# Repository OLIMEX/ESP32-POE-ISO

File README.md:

# ESP32-POE-ISO

ESP32-PoE-ISO is an IoT WIFI/BLE/Ethernet development board with Power-Over-Ethernet feature. The Si3402-B chip is IEEE 802.3-compliant, including pre-standard (legacy) PoE support. Perfect solution for Internet-of-Things that can be expanded with sensors and actuators taking power from Ethernet cable.

ESP32-POE-ISO has 3000VDC galvanic insulation from the Ethernet.

Product page: https://www.olimex.com/Products/IoT/ESP32/ESP32-POE-ISO/open-source-hardware

LICENSEE:

ESP32-POE-ISO is Open Source Hardware as per OSHWA.org definition. It is distributed with CERN OSH Licensee v1.2 which is available in the root directory of this repository.

The software examples for ESP32-POE-ISO are distributed with GPL v3 Licensee.

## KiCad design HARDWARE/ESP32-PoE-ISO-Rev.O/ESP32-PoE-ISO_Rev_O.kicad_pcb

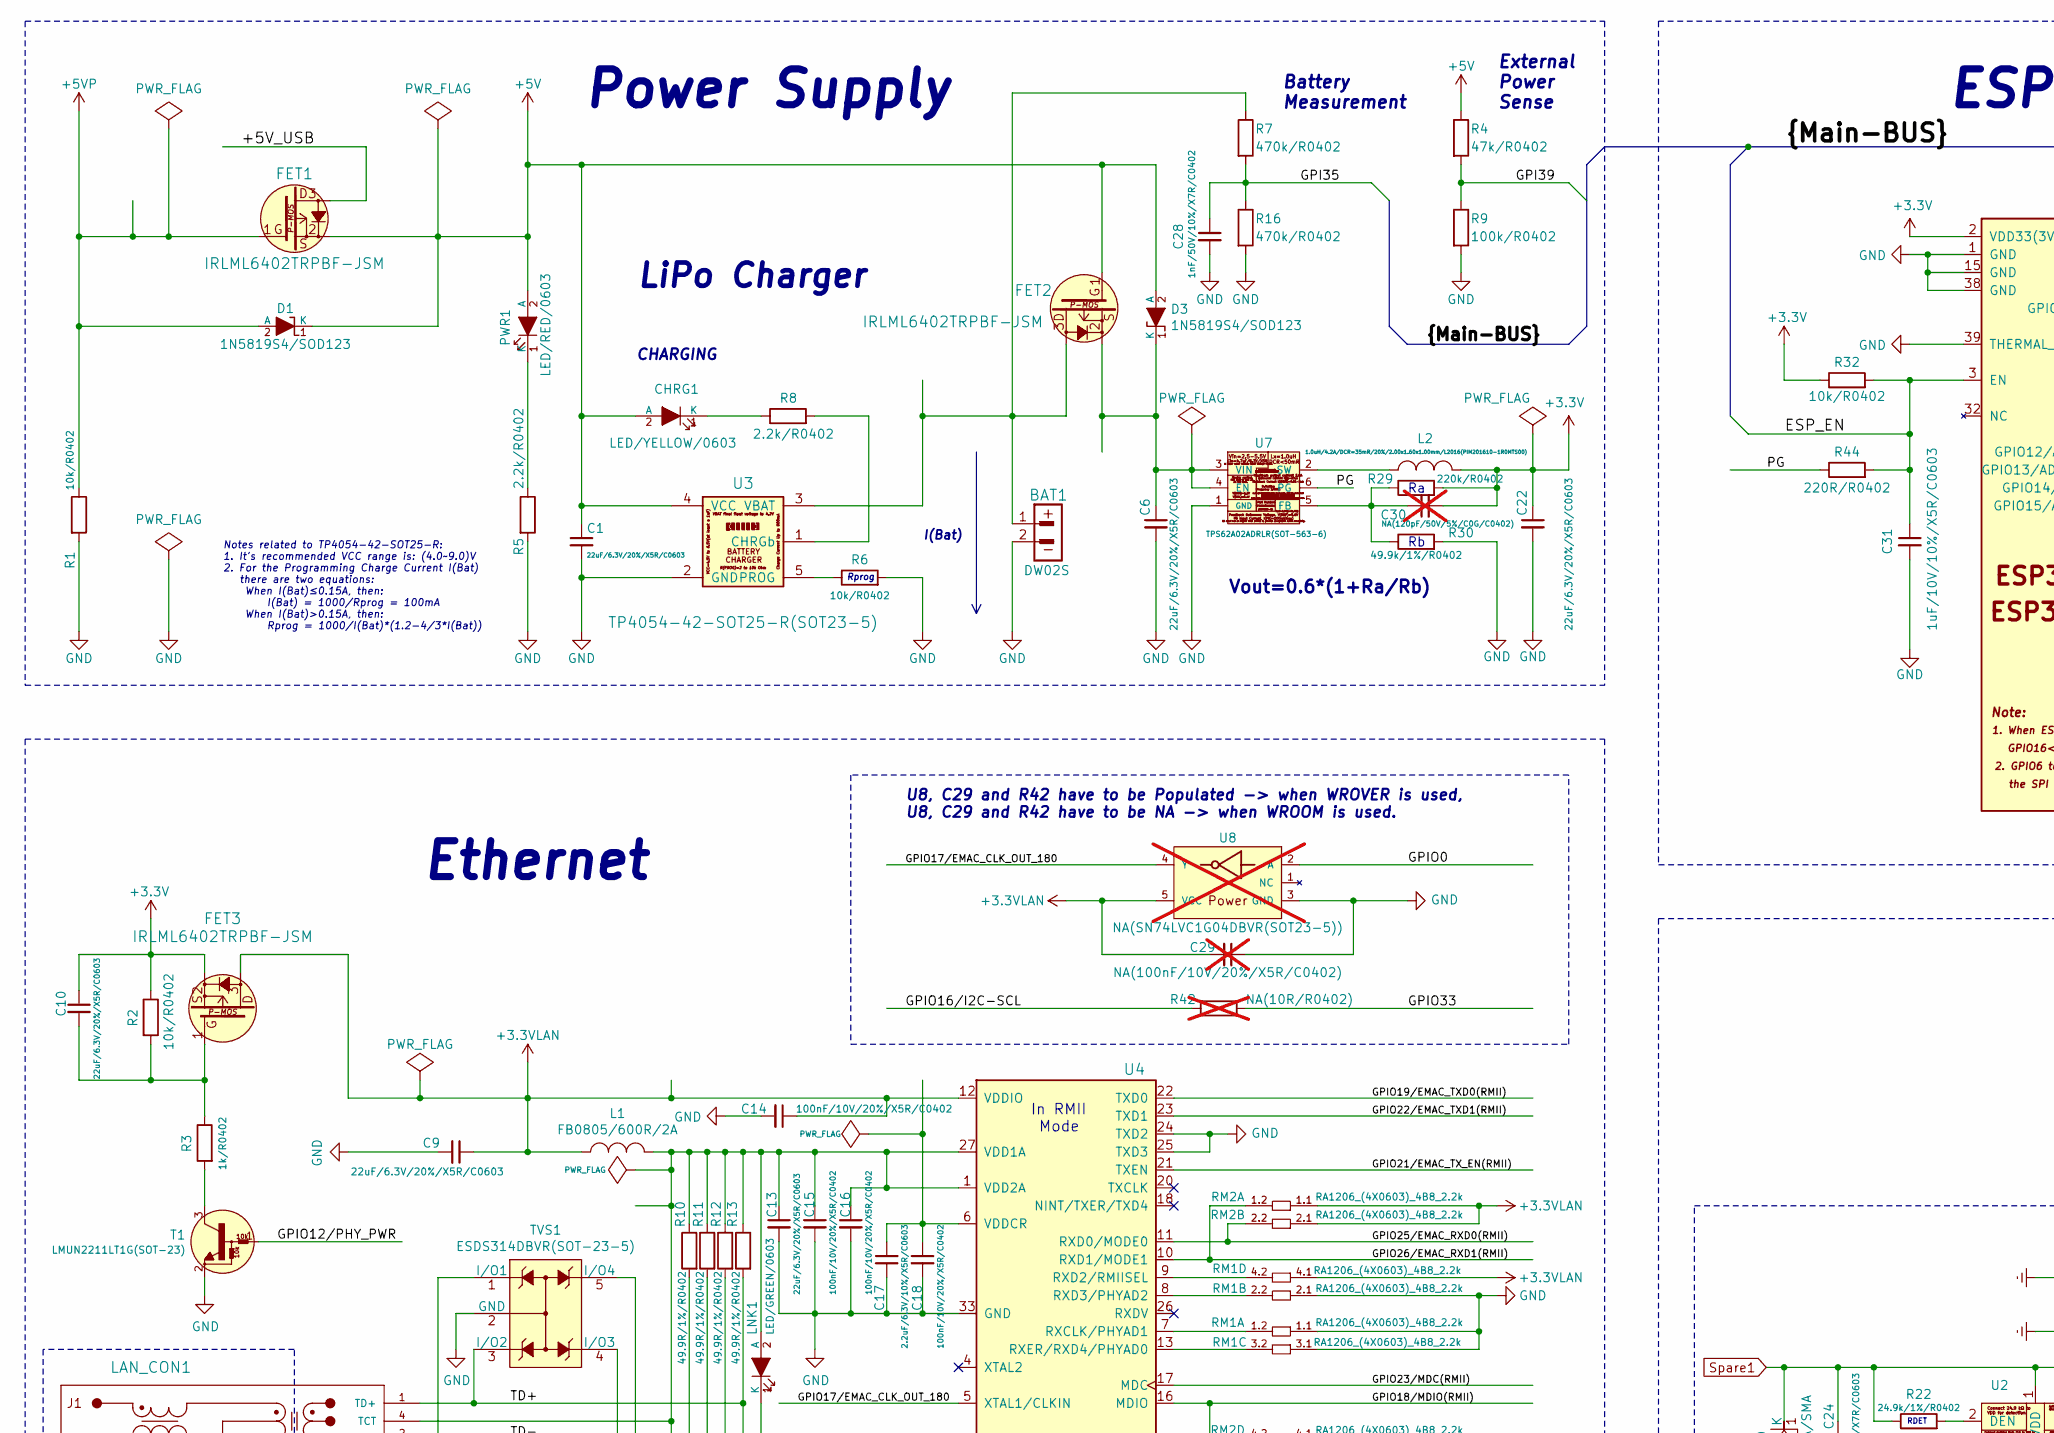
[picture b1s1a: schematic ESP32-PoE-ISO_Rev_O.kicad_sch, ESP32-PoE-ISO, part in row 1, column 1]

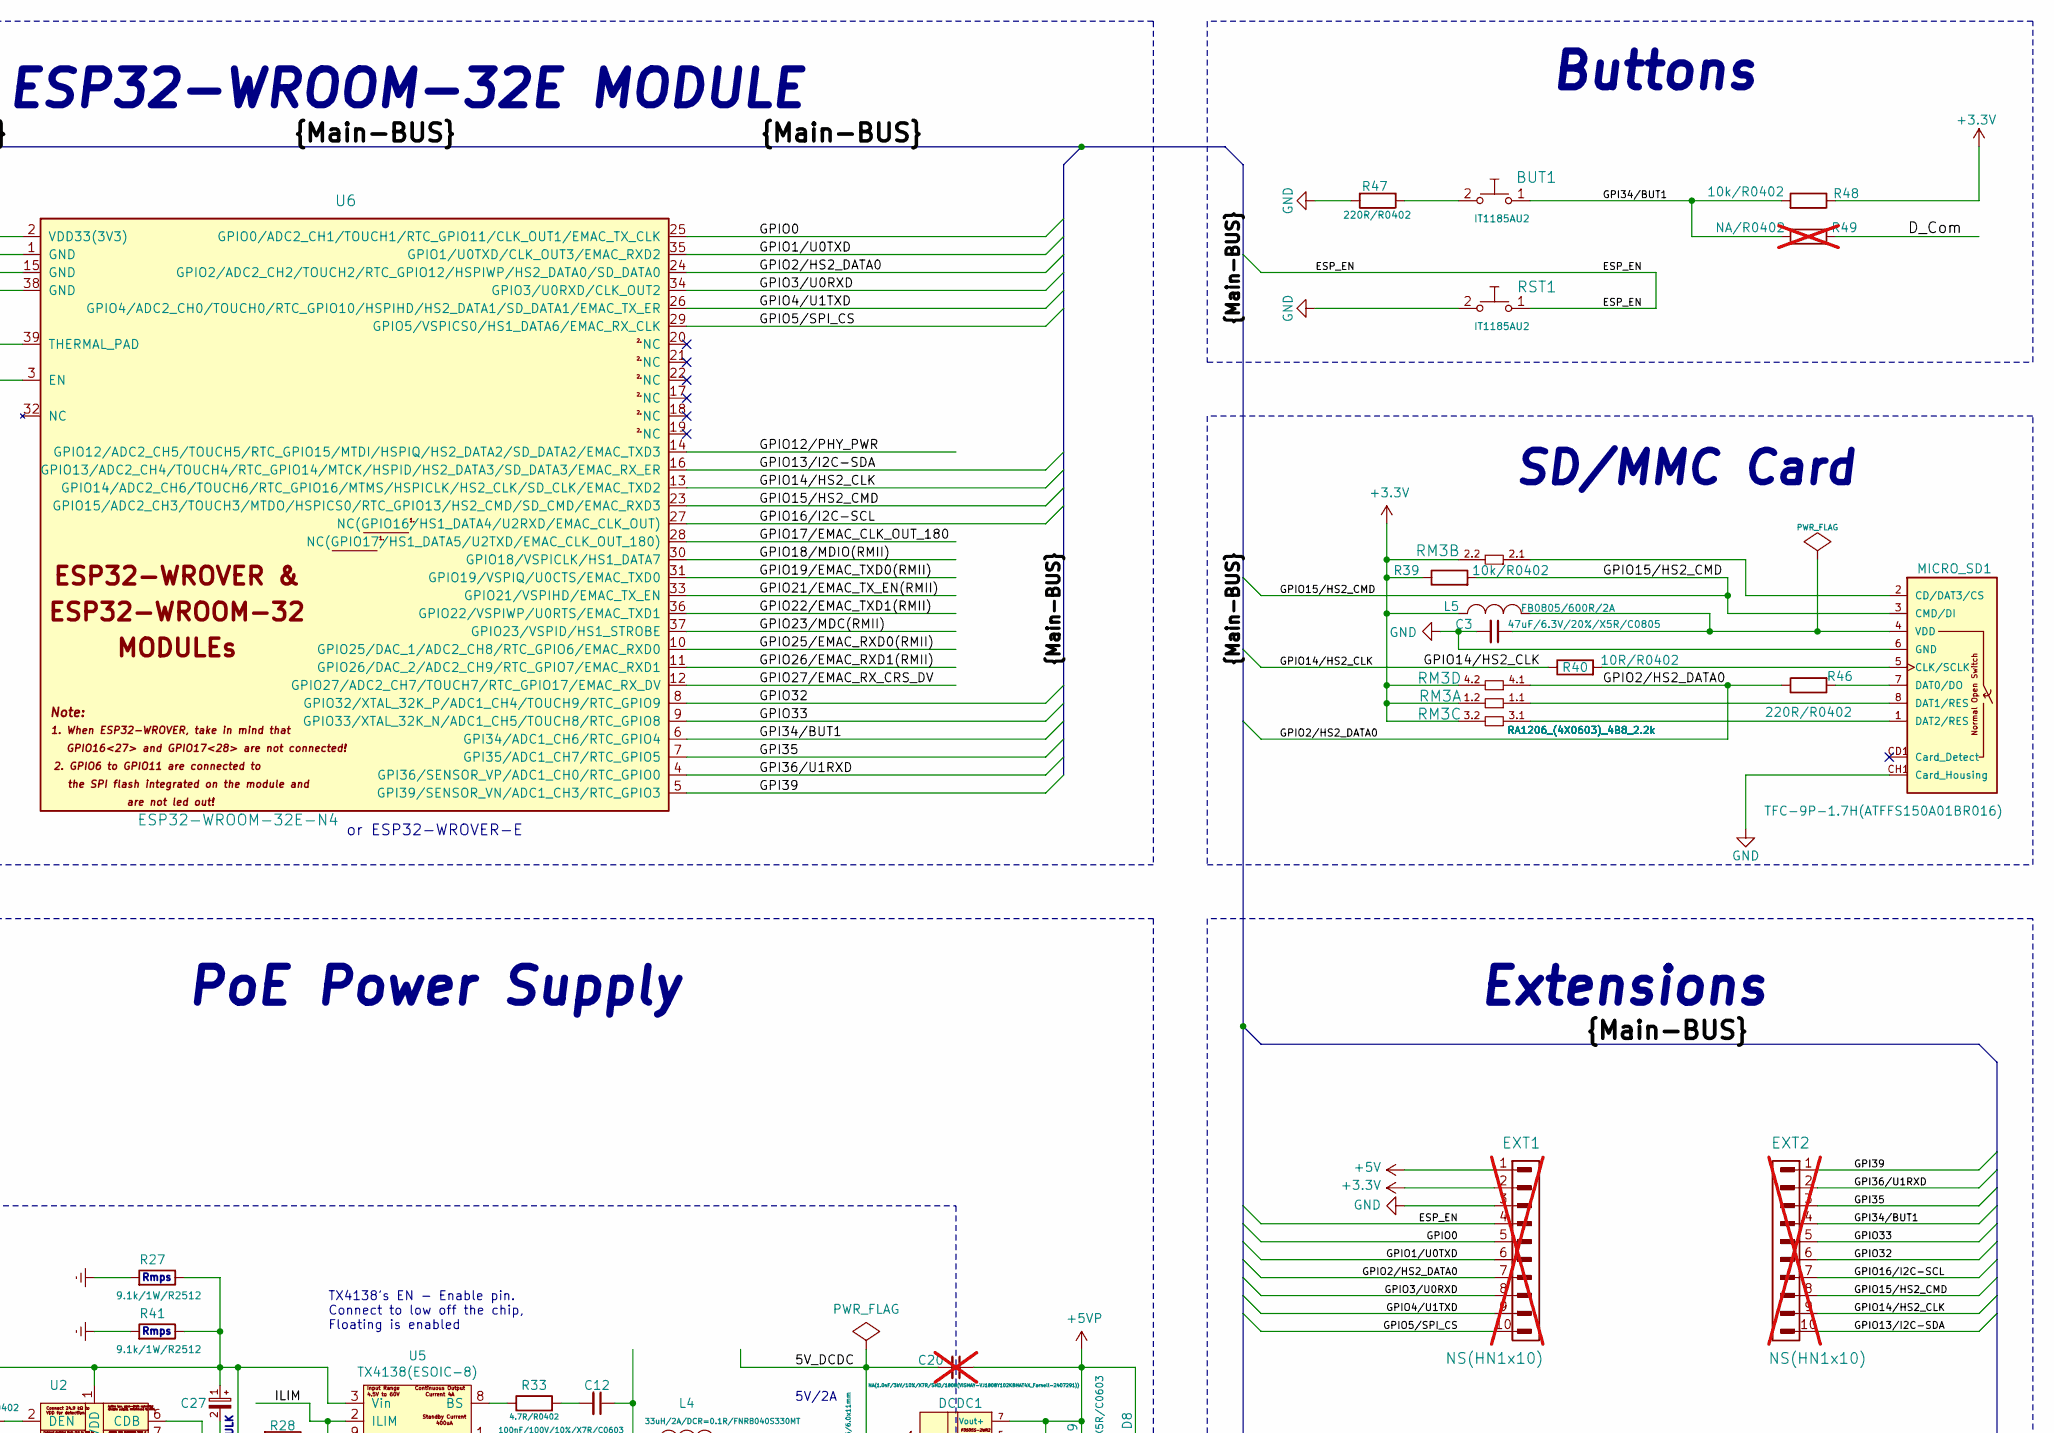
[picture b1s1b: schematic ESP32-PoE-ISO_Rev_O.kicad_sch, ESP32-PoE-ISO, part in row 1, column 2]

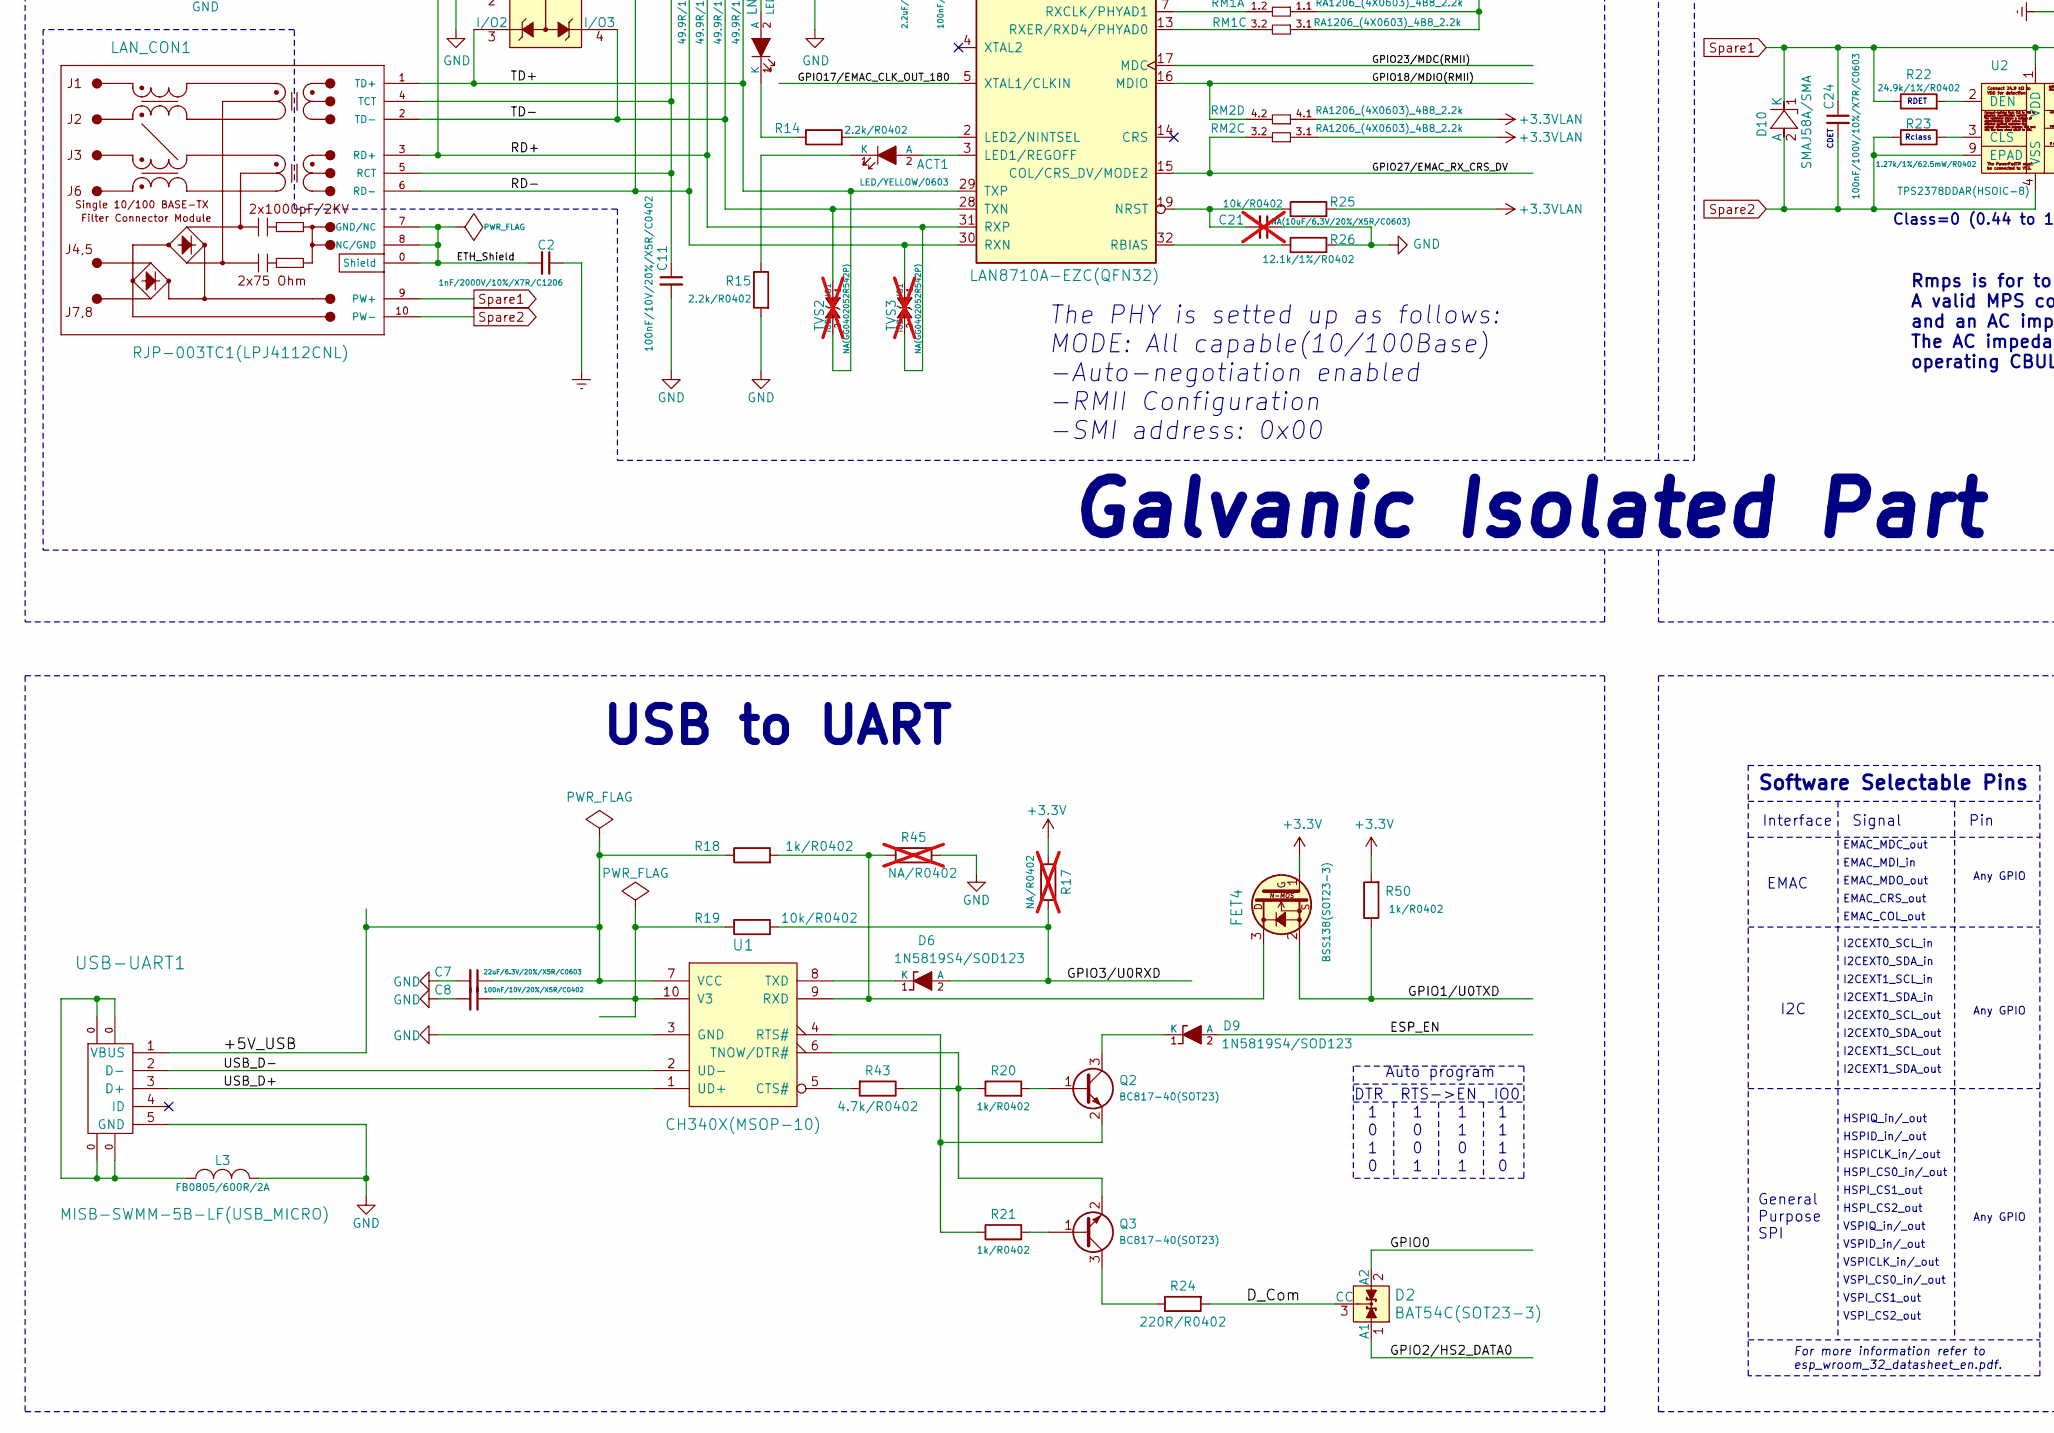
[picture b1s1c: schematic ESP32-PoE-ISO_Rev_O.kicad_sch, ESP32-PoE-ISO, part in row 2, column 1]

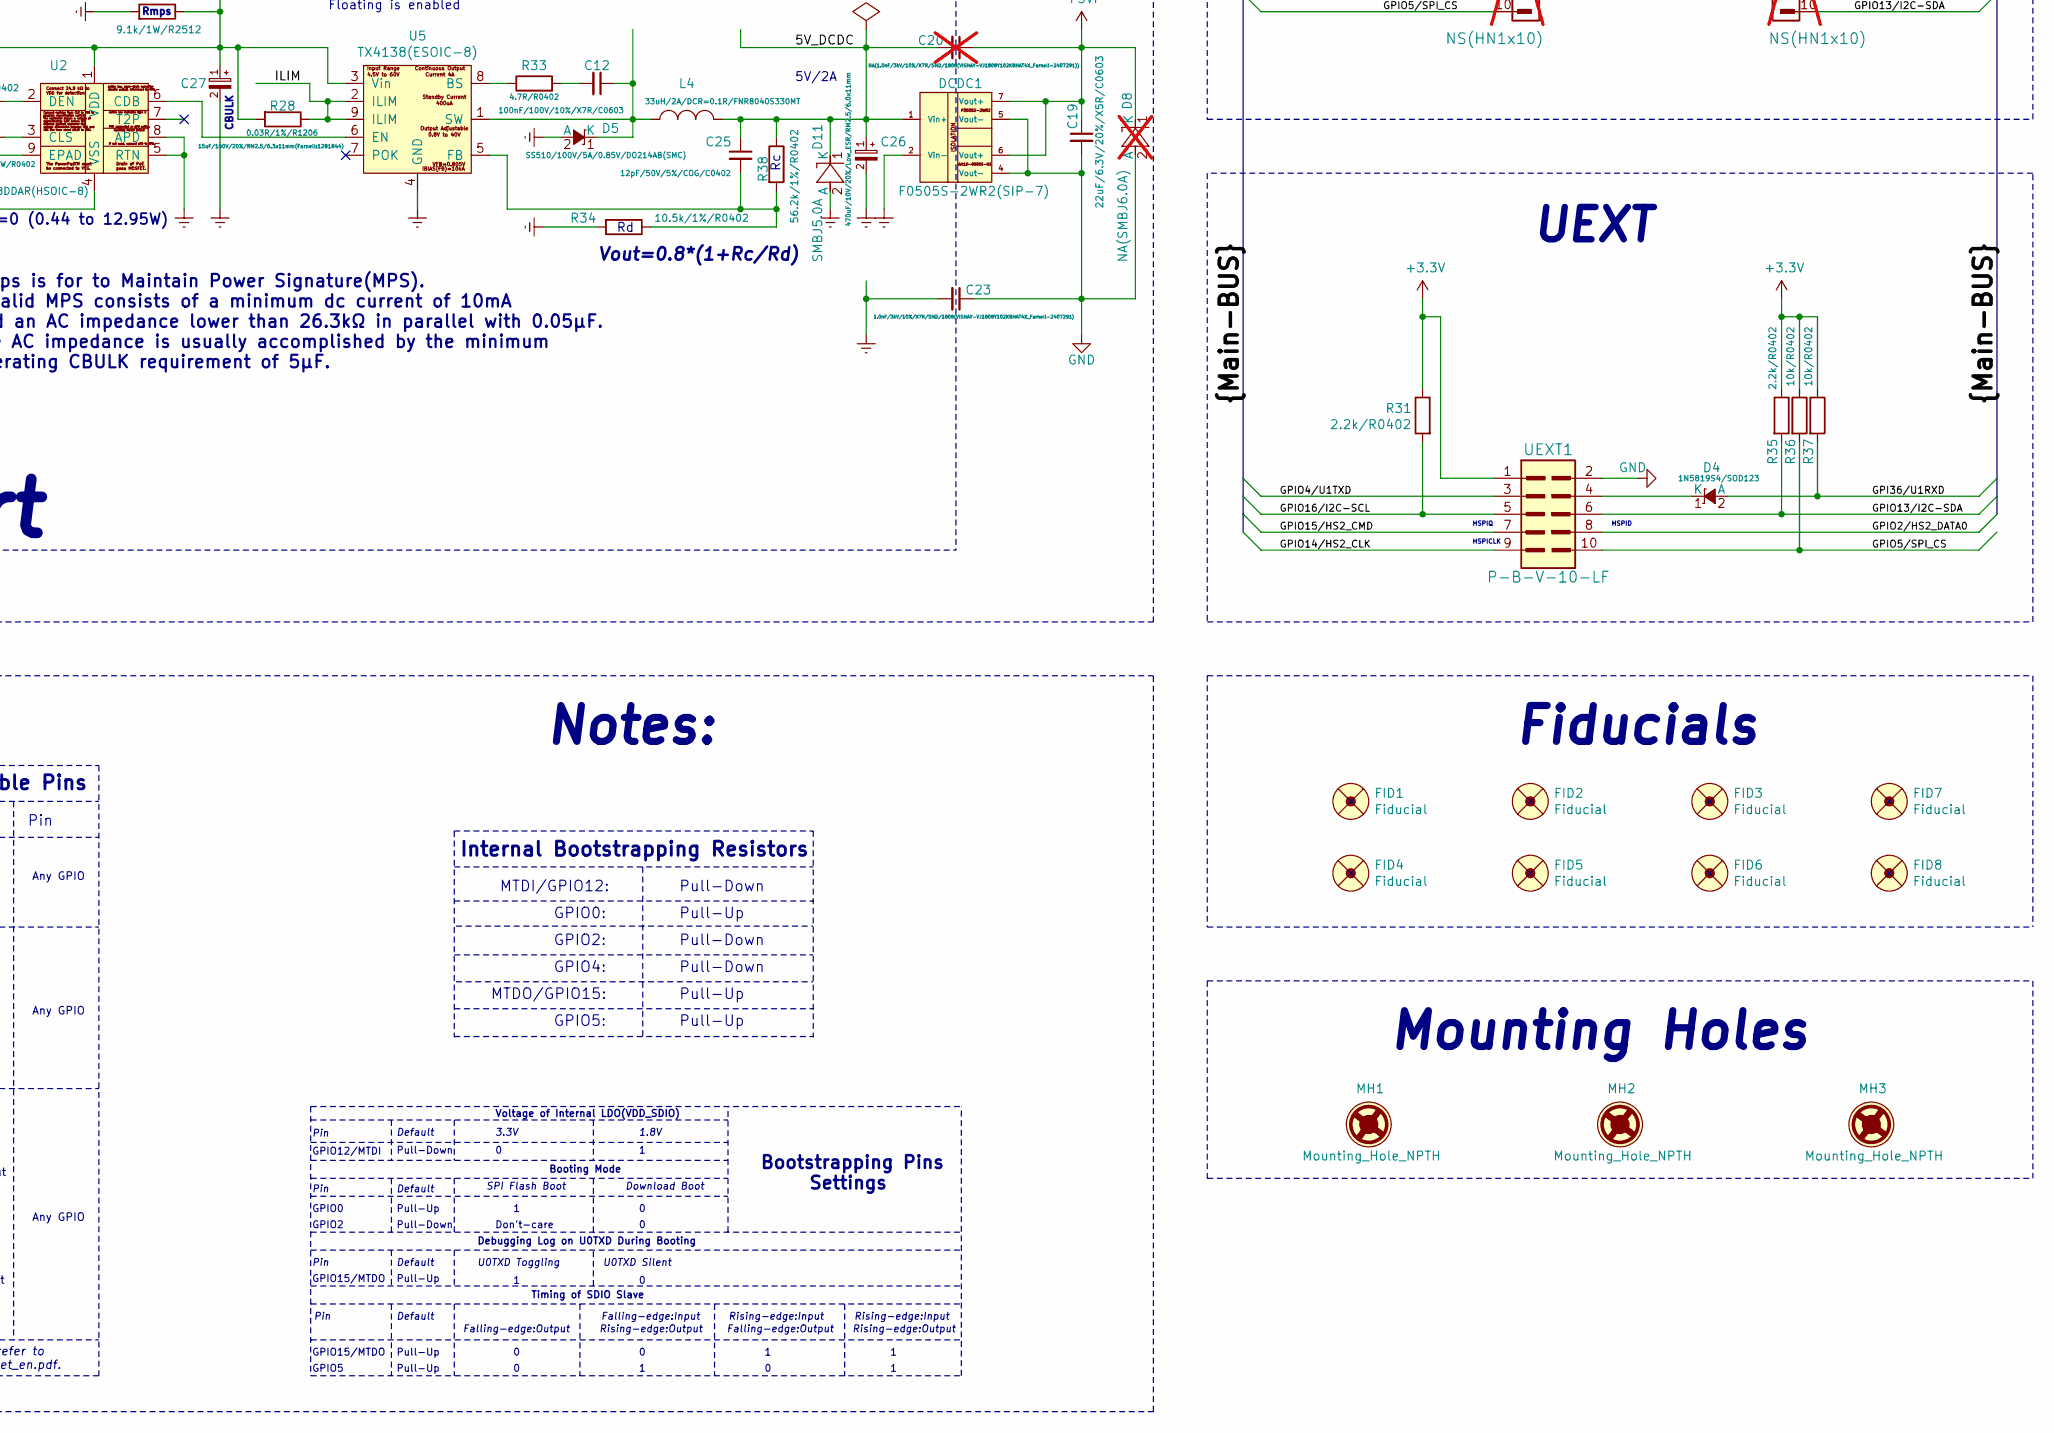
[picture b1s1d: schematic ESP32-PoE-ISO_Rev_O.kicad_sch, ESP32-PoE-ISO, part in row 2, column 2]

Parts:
ACT1: LED/YELLOW/0603; LED_0603_KA
BAT1: DW02S; LIPO_BAT_VERTICAL_DW02S
BUT1: IT1185AU2; IT1185AU2_V2
C1, C6, C7, C9, C10, C13, C19, C22: 22uF/6.3V/20%/X5R/C0603; C_0603_5MIL_DWS
C2: 1nF/2000V/10%/X7R/C1206; C_1206_5MIL_DWS_ISO
C3: 47uF/6.3V/20%/X5R/C0805; C_0805_5MIL_DWS
C8, C11, C14, C15, C16, C18: 100nF/10V/20%/X5R/C0402; C_0402_5MIL_DWS
C12, C24: 100nF/100V/10%/X7R/C0603; C_0603_5MIL_DWS
C17: 2.2uF/6.3V/10%/X5R/C0603; C_0603_5MIL_DWS
C20: NA(1.0nF/3kV/10%/X7R/SMD/1808(VISHAY-VJ1808Y102KB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; C_1808(4520)_5MIL_DWS_ISO; not fitted
C21: NA(10uF/6.3V/20%/X5R/C0603); C_0603_5MIL_DWS; not fitted
C23: 1.0nF/3kV/10%/X7R/SMD/1808(VISHAY-VJ1808Y102KBHAT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; C_1808(4520)_5MIL_DWS_ISO
C25: 12pF/50V/5%/COG/C0402; C_0402_5MIL_DWS
C26: 470uF/10V/20%/Low_ESR/RM2.5/6.0x11mm; CPOL-RM2.5mm_6.3x11mm_PTH
C27: 15uF/100V/20%/RM2.5/6.3x11mm(Farnell:1281844); CPOL-RM2.5mm_6.3x11mm_PTH
C28: 1nF/50V/10%/X7R/C0402; C_0402_5MIL_DWS
C29: NA(100nF/10V/20%/X5R/C0402); C_0402_5MIL_DWS; not fitted
C30: NA(120pF/50V/5%/C0G/C0402); C_0402_5MIL_DWS; not fitted
C31: 1uF/10V/10%/X5R/C0603; C_0603_5MIL_DWS
CHRG1: LED/YELLOW/0603; LED_0603_KA
D1, D3, D4, D6, D9: 1N5819S4/SOD123; SOD-123_1C-2A_KA
D2: BAT54C(SOT23-3); SOT23-3
D5: SS510/100V/5A/0.85V/DO214AB(SMC); DO214AB(SMC)_1(K)-2(A)
D8: NA(SMBJ6.0A); DO214AA_1(K)-2(A); not fitted
D10: SMAJ58A/SMA; SMA-KA
D11: SMBJ5.0A; DO214AA_1(K)-2(A)
DCDC1: F0505S-2WR2(SIP-7); SIP-7_Universal
EXT1, EXT2: NS(HN1x10); HN1x10; not fitted
FET1, FET2, FET3: IRLML6402TRPBF-JSM; SOT23
FET4: BSS138(SOT23-3); SOT23
FID1, FID4, FID7, FID8: Fiducial; Fiducial1x3_Paste
FID2, FID3, FID5, FID6: Fiducial; Fiducial1x3
L1, L3, L5: FB0805/600R/2A; L_0805_5MIL_DWS
L2: 1.0uH/4.2A/DCR=35mR/20%/2.00x1.60x1.00mm/L2016(PI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; L_2016_MM
L4: 33uH/2A/DCR=0.1R/FNR8040S330MT; FNR8040S
LAN_CON1: RJP-003TC1(LPJ4112CNL)
LNK1: LED/GREEN/0603; LED_0603_KA
MH1, MH2, MH3: Mounting_Hole_NPTH; NPTH_2.2mm
MICRO_SD1: TFC-9P-1.7H(ATFFS150A01BR016); uSD(TFC-9P-1.xH(ATFFS150A01BR016))
PWR1: LED/RED/0603; LED_0603_KA
Q2, Q3: BC817-40(SOT23); SOT23
R1, R2, R6, R19, R25, R32, R36, R37, R39, R48: 10k/R0402; R_0402_5MIL_DWS
R3, R18, R20, R21, R50: 1k/R0402; R_0402_5MIL_DWS
R4: 47k/R0402; R_0402_5MIL_DWS
R5, R8, R14, R15, R31, R35: 2.2k/R0402; R_0402_5MIL_DWS
R7, R16: 470k/R0402; R_0402_5MIL_DWS
R9: 100k/R0402; R_0402_5MIL_DWS
R10, R11, R12, R13: 49.9R/1%/R0402; R_0402_5MIL_DWS
R17, R45, R49: NA/R0402; R_0402_5MIL_DWS; not fitted
R22: 24.9k/1%/R0402; R_0402_5MIL_DWS
R23: 1.27k/1%/62.5mW/R0402; R_0402_5MIL_DWS
R24, R44, R46, R47: 220R/R0402; R_0402_5MIL_DWS
R26: 12.1k/1%/R0402; R_0402_5MIL_DWS
R27, R41: 9.1k/1W/R2512; R_2512_MM_DWS
R28: 0.03R/1%/R1206; R_1206_5MIL_DWS
R29: 220k/R0402; R_0402_5MIL_DWS
R30: 49.9k/1%/R0402; R_0402_5MIL_DWS
R33: 4.7R/R0402; R_0402_5MIL_DWS
R34: 10.5k/1%/R0402; R_0402_5MIL_DWS
R38: 56.2k/1%/R0402; R_0402_5MIL_DWS
R40: 10R/R0402; R_0402_5MIL_DWS
R42: NA(10R/R0402); R_0402_5MIL_DWS; not fitted
R43: 4.7k/R0402; R_0402_5MIL_DWS
RM1, RM2, RM3: RA1206_(4X0603)_4B8_2.2k; R_MATRIX_4
RST1: IT1185AU2; IT1185AU2_V2
T1: LMUN2211LT1G(SOT-23); SOT23
TVS1: ESDS314DBVR(SOT-23-5); SOT-23-5
TVS2, TVS3: NA(GG0402052R542P); D_0402_5MIL_DWS; not fitted
U1: CH340X(MSOP-10); MSOP-10_Pitch-0.5mm_3.00x3.00x1.00mm
U2: TPS2378DDAR(HSOIC-8); ESOIC-8
U3: TP4054-42-SOT25-R(SOT23-5); SOT-23-5
U4: LAN8710A-EZC(QFN32); QFN32_EP(33)_5.00x5.00x0.90mm_Pitch_0.50mm
U5: TX4138(ESOIC-8); ESOIC-8
U6: ESP32-WROOM-32E-N4; ESP32-WROVER_MODULE
U7: TPS62A02ADRLR(SOT-563-6); SOT-563-6
U8: NA(SN74LVC1G04DBVR(SOT23-5)); SOT-23-5; not fitted
UEXT1: P-B-V-10-LF; GBH-254-SMT-10
USB-UART1: MISB-SWMM-5B-LF(USB_MICRO); USB-MICRO_MISB-SWMM-5B_LF

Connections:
+3.3V: C10.1, C22.1, C30.2, EXT1.2, FET3.2, FET4.1 (G), L2.2, L5.1, R2.1, R17.1, R29.2, R31.1, R32.1, R35.1, R36.1, R37.1, R39.1, R48.1, R50.2, RM3.1.2, RM3.2.2, RM3.3.2, RM3.4.2, U6.2 (VDD33(3V3)), UEXT1.1
+3.3VLAN: C9.1, C14.1, C29.2, FET3.3, L1.1, R25.2, RM1.4.1, RM2.1.1, RM2.2.1, RM2.3.1, RM2.4.1, U4.12 (VDDIO), U8.5 (VCC)
+5V: C1.1, CHRG1.2 (A), D1.1 (K), D3.2 (A), EXT1.1, FET1.2, FET2.1, PWR1.2 (A), R4.1, U3.4 (VCC)
+5VP: C19.1, C20.1, D1.2 (A), D8.1 (K), DCDC1.6 (Vout+), DCDC1.7 (Vout+), FET1.1, R1.1
/5V_DCDC: C20.2, C25.1, C26.1 (+), D11.1 (K), DCDC1.1 (Vin+), L4.2, R38.1
/+5V_USB: C7.1, FET1.3, R18.1, U1.7 (VCC), USB-UART1.1 (VBUS)
/D_Com: D2.3 (CC), R24.2, R49.2
/ESP_EN: C31.1, D9.2 (A), EXT1.4, R32.2, R44.2, RST1.1, U6.3 (EN)
/ETH_Shield: C2.2, LAN_CON1.0 (Shield), LAN_CON1.7 (GND/NC), LAN_CON1.8 (NC/GND)
/GPI34/BUT1: BUT1.1, EXT2.4, R48.2, R49.1, U6.6 (GPI34/ADC1_CH6/RTC_GPIO4)
/GPI35: C28.1, EXT2.3, R7.2, R16.1, U6.7 (GPI35/ADC1_CH7/RTC_GPIO5)
/GPI36/U1RXD: D4.2 (A), EXT2.2, R37.2, U6.4 (GPI36/SENSOR_VP/ADC1_CH0/RTC_GPIO0)
/GPI39: EXT2.1, R4.2, R9.1, U6.5 (GPI39/SENSOR_VN/ADC1_CH3/RTC_GPIO3)
/GPIO0: D2.2 (A2), EXT1.5, U6.25 (GPIO0/ADC2_CH1/TOUCH1/RTC_GPIO11/CLK_OU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), U8.2 (A)
/GPIO1/U0TXD: EXT1.6, FET4.2 (S), R50.1, U6.35 (GPIO1/U0TXD/CLK_OUT3/EMAC_RXD2)
/GPIO2/HS2_DATA0: D2.1 (A1), EXT1.7, R46.1, RM3.4.1, U6.24 (GPIO2/ADC2_CH2/TOUCH2/RTC_GPIO12/HSPIWP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), UEXT1.8
/GPIO3/U0RXD: D6.2 (A), EXT1.8, R17.2, R19.2, U6.34 (GPIO3/U0RXD/CLK_OUT2)
/GPIO4/U1TXD: EXT1.9, U6.26 (GPIO4/ADC2_CH0/TOUCH0/RTC_GPIO10/HSPIHD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), UEXT1.3
/GPIO5/SPI_CS: EXT1.10, R36.2, U6.29 (GPIO5/VSPICS0/HS1_DATA6/EMAC_RX_CLK), UEXT1.10
/GPIO12/PHY_PWR: T1.1 (B), U6.14 (GPIO12/ADC2_CH5/TOUCH5/RTC_GPIO15/MTDI/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)
/GPIO13/I2C-SDA: EXT2.10, R35.2, U6.16 (GPIO13/ADC2_CH4/TOUCH4/RTC_GPIO14/MTCK/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), UEXT1.6
/GPIO14/HS2_CLK: EXT2.9, R40.1, U6.13 (GPIO14/ADC2_CH6/TOUCH6/RTC_GPIO16/MTMS/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), UEXT1.9
/GPIO15/HS2_CMD: EXT2.8, MICRO_SD1.3 (CMD/DI), R39.2, U6.23 (GPIO15/ADC2_CH3/TOUCH3/MTDO/HSPICS0/RTC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), UEXT1.7
/GPIO16/I2C-SCL: EXT2.7, R31.2, R42.2, U6.27 (NC(GPIO16/HS1_DATA4/U2RXD/EMAC_CLK_OUT)), UEXT1.5
/GPIO17/EMAC_CLK_OUT_180: U4.5 (XTAL1/CLKIN), U6.28 (NC(GPIO17/HS1_DATA5/U2TXD/EMAC_CLK_OUT_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), U8.4 (Y)
/GPIO18/MDIO(RMII): RM2.4.2, U4.16 (MDIO), U6.30 (GPIO18/VSPICLK/HS1_DATA7)
/GPIO19/EMAC_TXD0(RMII): U4.22 (TXD0), U6.31 (GPIO19/VSPIQ/U0CTS/EMAC_TXD0)
/GPIO21/EMAC_TX_EN(RMII): U4.21 (TXEN), U6.33 (GPIO21/VSPIHD/EMAC_TX_EN)
/GPIO22/EMAC_TXD1(RMII): U4.23 (TXD1), U6.36 (GPIO22/VSPIWP/U0RTS/EMAC_TXD1)
/GPIO23/MDC(RMII): U4.17 (MDC), U6.37 (GPIO23/VSPID/HS1_STROBE)
/GPIO25/EMAC_RXD0(RMII): RM2.2.2, U4.11 (RXD0/MODE0), U6.10 (GPIO25/DAC_1/ADC2_CH8/RTC_GPIO6/EMAC_RX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)
/GPIO26/EMAC_RXD1(RMII): RM2.1.2, U4.10 (RXD1/MODE1), U6.11 (GPIO26/DAC_2/ADC2_CH9/RTC_GPIO7/EMAC_RX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)
/GPIO27/EMAC_RX_CRS_DV: RM2.3.2, U4.15 (COL/CRS_DV/MODE2), U6.12 (GPIO27/ADC2_CH7/TOUCH7/RTC_GPIO17/EMAC_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)
/GPIO32: EXT2.6, U6.8 (GPIO32/XTAL_32K_P/ADC1_CH4/TOUCH9/RTC_G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)
/GPIO33: EXT2.5, R42.1, U6.9 (GPIO33/XTAL_32K_N/ADC1_CH5/TOUCH8/RTC_G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)
/ILIM: R28.1, U5.2 (ILIM), U5.9 (ILIM)
/PG: R44.1, U7.6 (PG)
/RD+: LAN_CON1.3 (RD+), R11.2, TVS1.1 (I/O1), TVS3.2 (IO2), U4.31 (RXP)
/RD-: LAN_CON1.6 (RD-), R10.2, TVS1.5 (I/O4), TVS3.1 (IO1), U4.30 (RXN)
/TD+: LAN_CON1.1 (TD+), R13.2, TVS1.3 (I/O2), TVS2.2 (IO2), U4.29 (TXP)
/TD-: LAN_CON1.2 (TD-), R12.2, TVS1.4 (I/O3), TVS2.1 (IO1), U4.28 (TXN)
/USB_D+: U1.1 (UD+), USB-UART1.3 (D+)
/USB_D-: U1.2 (UD-), USB-UART1.2 (D-)
Earth: C2.1, C23.2, C26.2 (-), C27.2 (-), D5.2 (A), D11.2 (A), DCDC1.2 (Vin-), R27.2, R34.2, R41.2, U2.5 (RTN), U2.8 (APD), U5.4 (GND)
GND: BAT1.2, C1.2, C3.2, C6.2, C7.2, C8.2, C9.2, C11.2, C13.2, C14.2, C15.2, C16.2, C17.2, C18.2, C19.2, C21.1, C22.2, C23.1, C28.2, C29.1, C31.2, D8.2 (A), DCDC1.4 (Vout-), DCDC1.5 (Vout-), EXT1.3, L3.2, MICRO_SD1.6 (GND), MICRO_SD1.CH1 (Card_Housing), R1.2, R5.2, R6.2, R9.2, R15.2, R16.2, R26.2, R30.2, R45.2, R47.2, RM1.1.1, RM1.2.1, RM1.3.1, RST1.2, T1.2 (E), TVS1.2 (GND), U1.3 (GND), U3.2 (GND), U4.24 (TXD2), U4.25 (TXD3), U4.33 (GND), U6.1 (GND), U6.15 (GND), U6.38 (GND), U6.39 (THERMAL_PAD), U7.1 (GND), U8.3 (GND), UEXT1.2, USB-UART1.5 (GND)
unnamed: ACT1.2 (A), U4.3 (LED1/REGOFF)
unnamed: ACT1.1 (K), R15.1
unnamed: BUT1.2, R47.1
unnamed: C10.2, FET3.1, R2.2, R3.1
unnamed: C12.2, R33.2
unnamed: CHRG1.1 (K), R8.1
unnamed: C6.1, D3.1 (K), FET2.2, U7.3 (VIN), U7.4 (EN)
unnamed: D4.1 (K), UEXT1.4
unnamed: C12.1, D5.1 (K), L4.1, U5.1 (SW)
unnamed: D6.1 (K), U1.8 (TXD)
unnamed: D9.1 (K), Q2.3 (C)
unnamed: FET4.3 (D), R18.2, R45.1, U1.9 (RXD)
unnamed: L3.1, USB-UART1.0
unnamed: C11.1, C13.1, C15.1, C16.1, L1.2, LAN_CON1.4 (TCT), LAN_CON1.5 (RCT), LNK1.2 (A), R10.1, R11.1, R12.1, R13.1, U4.1 (VDD2A), U4.27 (VDD1A)
unnamed: LNK1.1 (K), R14.1
unnamed: MICRO_SD1.2 (CD/DAT3/CS), RM3.2.1
unnamed: MICRO_SD1.5 (CLK/SCLK), R40.2
unnamed: MICRO_SD1.7 (DAT0/DO), R46.2
unnamed: MICRO_SD1.8 (DAT1/RES), RM3.1.1
unnamed: MICRO_SD1.1 (DAT2/RES), RM3.3.1
unnamed: C3.1, L5.2, MICRO_SD1.4 (VDD)
unnamed: PWR1.1 (K), R5.1
unnamed: Q2.1 (B), R20.2
unnamed: Q2.2 (E), R21.1, U1.4 (RTS#)
unnamed: Q3.1 (B), R21.2
unnamed: Q3.3 (C), R24.1
unnamed: Q3.2 (E), R20.1, R43.1, U1.6 (TNOW/DTR#)
unnamed: R3.2, T1.3 (C)
unnamed: R43.2, U1.5 (CTS#)
unnamed: C8.1, R19.1, U1.10 (V3)
unnamed: U2.6 (CDB), U5.6 (EN)
unnamed: R23.1, U2.3 (CLS)
unnamed: R22.2, U2.2 (DEN)
unnamed: R8.2, U3.1 (CHRGb)
unnamed: R6.1, U3.5 (PROG)
unnamed: BAT1.1, FET2.3, R7.1, U3.3 (VBAT)
unnamed: R14.2, U4.2 (LED2/NINTSEL)
unnamed: C21.2, R25.1, U4.19 (NRST)
unnamed: R26.1, U4.32 (RBIAS)
unnamed: RM1.1.2, U4.7 (RXCLK/PHYAD1)
unnamed: RM1.4.2, U4.9 (RXD2/RMIISEL)
unnamed: RM1.2.2, U4.8 (RXD3/PHYAD2)
unnamed: RM1.3.2, U4.13 (RXER/RXD4/PHYAD0)
unnamed: C17.1, C18.1, U4.6 (VDDCR)
unnamed: R33.1, U5.8 (BS)
unnamed: C25.2, R34.1, R38.2, U5.5 (FB)
unnamed: C30.1, R29.1, R30.1, U7.5 (FB)
unnamed: L2.1, U7.2 (SW)
Spare1: C24.1, C27.1 (+), D10.1 (K), LAN_CON1.9 (PW+), R22.1, R27.1, R28.2, R41.1, U2.1 (VDD), U5.3 (Vin)
Spare2: C24.2, D10.2 (A), LAN_CON1.10 (PW-), R23.2, U2.4 (VSS), U2.9 (EPAD)

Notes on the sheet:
Don't-care
CHARGING
General Purpose SPI
Pull-Down
Default
LiPo Charger
EMAC_MDC_out
Software Selectable Pins
Rmps
ESP32-WROOM-32E MODULE
VSPID_in/_out
Bootstrapping Pins Settings
Class=0 (0.44 to 12.95W)
MTDI/GPIO12:
GPIO0
I2CEXT0_SCL_in
Any GPIO
EMAC_MDI_in
Falling-edge:Input
VSPICLK_in/_out
HSPI_CS1_out
GPIO15/MTDO
Internal Bootstrapping Resistors
Booting Mode
Mounting Holes
UEXT
USB to UART
Download Boot
EMAC_MDO_out
Falling-edge:Output
GPIO5:
External Power Sense
GPIO0:
SPI Flash Boot
TX4138's EN - Enable pin. Connect to low off the chip, Floating is enabled
Rclass
Extensions
or ESP32-WROVER-E
1.8V
I2CEXT1_SCL_in

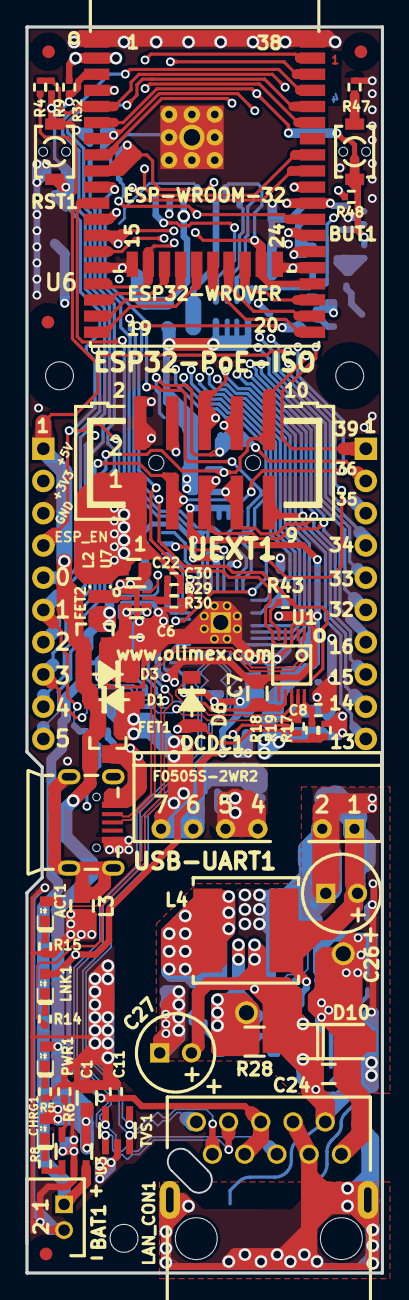
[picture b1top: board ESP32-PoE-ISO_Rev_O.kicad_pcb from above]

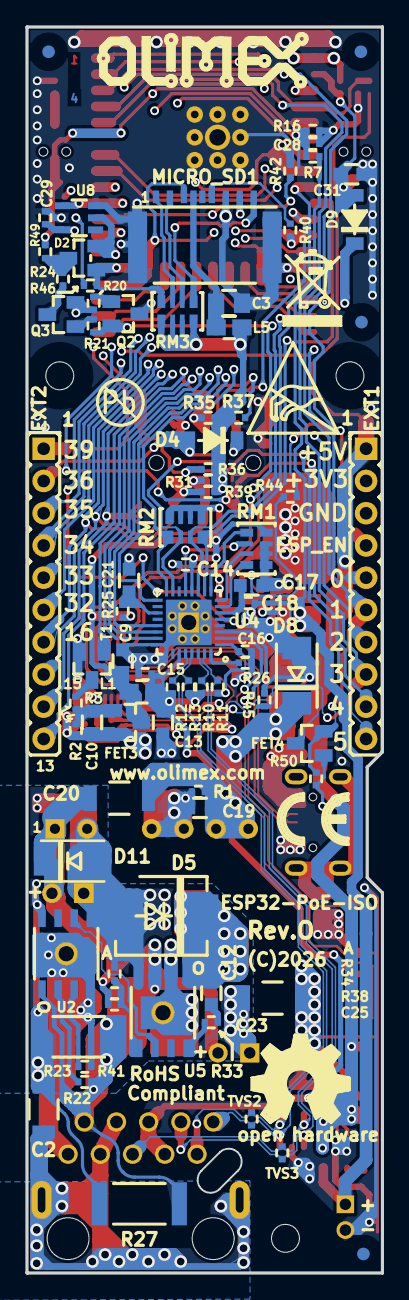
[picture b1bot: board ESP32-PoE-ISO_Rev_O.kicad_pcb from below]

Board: 4 copper layers, 28.0 x 98.2 mm, 147 parts (87 on the bottom side), 95 nets.

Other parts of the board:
Drill_Slot3: 2 mm; Mounting_hole_2_mm
Logo_OSHW: Sign_OSHW_8x8
Logo_Olimex: Logo_OLIMEX_TB
Sign_Antistatic: Val**; Sign_Antistatic
Sign_CE: CE_Sign
Sign_PB-Free: Sign_PB-Free
Sign_RecycleBin: Sign_RecycleBin_1

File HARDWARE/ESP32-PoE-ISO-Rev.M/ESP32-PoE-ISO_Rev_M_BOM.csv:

Quantity,Value,Footprint,Reference
2,LED/YELLOW/0603,LED_0603_KA,"ACT1, CHRG1"
1,DW02S,LIPO_BAT_VERTICAL_DW02S,BAT1
2,IT1185AU2,IT1185AU2_V2,"BUT1, RST1"
8,22uF/6.3V/20%/X5R/C0603,C_0603_5MIL_DWS,"C1, C6, C7, C9, C10, C13, C19, C22"
1,1nF/2000V/10%/X7R/C1206,C_1206_5MIL_DWS_ISO,C2
1,47uF/6.3V/20%/X5R/C0805,C_0805_5MIL_DWS,C3
6,100nF/10V/20%/X5R/C0402,C_0402_5MIL_DWS,"C8, C11, C14, C15, C16, C18"
2,100nF/100V/10%/X7R/C0603,C_0603_5MIL_DWS,"C12, C24"
1,2.2uF/6.3V/10%/X5R/C0603,C_0603_5MIL_DWS,C17
1,1.0nF/3kV/10%/X7R/SMD/1808(VISHAY-VJ1808Y102KBHAT4X_Farnell-2407291),C_1808(4520)_5MIL_DWS_ISO,C23
1,12pF/50V/5%/COG/C0402,C_0402_5MIL_DWS,C25
1,470uF/10V/20%/Low_ESR/RM2.5/6.0x11mm,CPOL-RM2.5mm_6.3x11mm_PTH,C26
1,15uF/100V/20%/RM2.5/6.3x11mm(Farnell:1281844),CPOL-RM2.5mm_6.3x11mm_PTH,C27
1,1nF/50V/10%/X7R/C0402,C_0402_5MIL_DWS,C28
1,1uF/10V/10%/X5R/C0603,C_0603_5MIL_DWS,C31
6,1N5819S4/SOD123,SOD-123_1C-2A_KA,"D1, D3, D4, D6, D7, D9"
1,BAT54C(SOT23-3),SOT23-3,D2
1,SS510/100V/5A/0.85V/DO214AB(SMC),DO214AB(SMC)_1(K)-2(A),D5
1,SMAJ58A/SMA,SMA-KA,D10
1,F0505S-2WR2(SIP-7),SIP-7_Universal,DCDC1
2,HN1x10,HN1x10,"EXT1, EXT2"
3,WPM2015-3/TR,SOT23,"FET1, FET2, FET3"
3,FB0805/600R/2A,L_0805_5MIL_DWS,"L1, L3, L5"
1,1.0uH/4.2A/DCR=35mR/20%/2.00x1.60x1.00mm/L2016(PIM201610-1R0MTS00),L_2016_MM,L2
1,33uH/2.1A/DCR=0.1R/20%/DBS135(PD3316MT330),DBS135,L4
1,RJP-003TC1(LPJ4112CNL),RJP-003TC1(LPJ4112CNL),LAN_CON1
1,LED/GREEN/0603,LED_0603_KA,LNK1
1,TFC-9P-1.7H(ATFFS150A01BR016),uSD(TFC-9P-1.xH(ATFFS150A01BR016)),MICRO_SD1
1,LED/RED/0603,LED_0603_KA,PWR1
2,BC817-40(SOT23),SOT23,"Q2, Q3"
11,10k/R0402,R_0402_5MIL_DWS,"R1, R2, R6, R18, R19, R25, R32, R36, R37, R39, R48"
3,1k/R0402,R_0402_5MIL_DWS,"R3, R20, R21"
1,47k/R0402,R_0402_5MIL_DWS,R4
6,2.2k/R0402,R_0402_5MIL_DWS,"R5, R8, R14, R15, R31, R35"
2,470k/R0402,R_0402_5MIL_DWS,"R7, R16"
1,100k/R0402,R_0402_5MIL_DWS,R9
4,49.9R/1%/R0402,R_0402_5MIL_DWS,"R10, R11, R12, R13"
1,24.9k/1%/R0402,R_0402_5MIL_DWS,R22
1,1.27k/1%/62.5mW/R0402,R_0402_5MIL_DWS,R23
3,220R/R0402,R_0402_5MIL_DWS,"R24, R46, R47"
1,12.1k/1%/R0402,R_0402_5MIL_DWS,R26
2,9.1k/1W/R2512,R_2512_MM_DWS,"R27, R41"
1,0.03R/1%/R1206,R_1206_5MIL_DWS,R28
1,220k/R0402,R_0402_5MIL_DWS,R29
1,49.9k/1%/R0402,R_0402_5MIL_DWS,R30
1,4.7R/R0402,R_0402_5MIL_DWS,R33
1,10.5k/1%/R0402,R_0402_5MIL_DWS,R34
1,56.2k/1%/R0402,R_0402_5MIL_DWS,R38
1,10R/R0402,R_0402_5MIL_DWS,R40
1,4.7k/R0402,R_0402_5MIL_DWS,R43
3,RA1206_(4X0603)_4B8_2.2k,R_MATRIX_4,"RM1, RM2, RM3"
1,LMUN2211LT1G(SOT-23),SOT23,T1
1,ESDS314DBVR(SOT-23-5),SOT-23-5,TVS1
1,CH340X(MSOP-10),MSOP-10_Pitch-0.5mm_3.00x3.00x1.00mm,U1
1,TPS2378DDAR(HSOIC-8),ESOIC-8,U2
1,TP4054-42-SOT25-R(SOT23-5),SOT-23-5,U3
1,LAN8710A-EZC(QFN32),QFN32_EP(33)_5.00x5.00x0.90mm_Pitch_0.50mm,U4
1,TX4138(ESOIC-8),ESOIC-8,U5
1," 	
ESP32-WROOM-32E-N4",ESP32-WROVER_MODULE,U6
1,TPS62A02ADRLR(SOT-563-6),SOT-563-6,U7
1,P-B-V-10-LF,GBH-254-SMT-10,UEXT1
1,MISB-SWMM-5B-LF(USB_MICRO),USB-MICRO_MISB-SWMM-5B_LF,USB-UART1

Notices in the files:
HARDWARE/ESP32-PoE-ISO-Rev.D/ESP32-PoE-ISO_Rev_D.kicad_pcb:
(C) 2019
HARDWARE/ESP32-PoE-ISO-Rev.O/ESP32-PoE-ISO_Rev_O.kicad_pcb:
(C)2026
